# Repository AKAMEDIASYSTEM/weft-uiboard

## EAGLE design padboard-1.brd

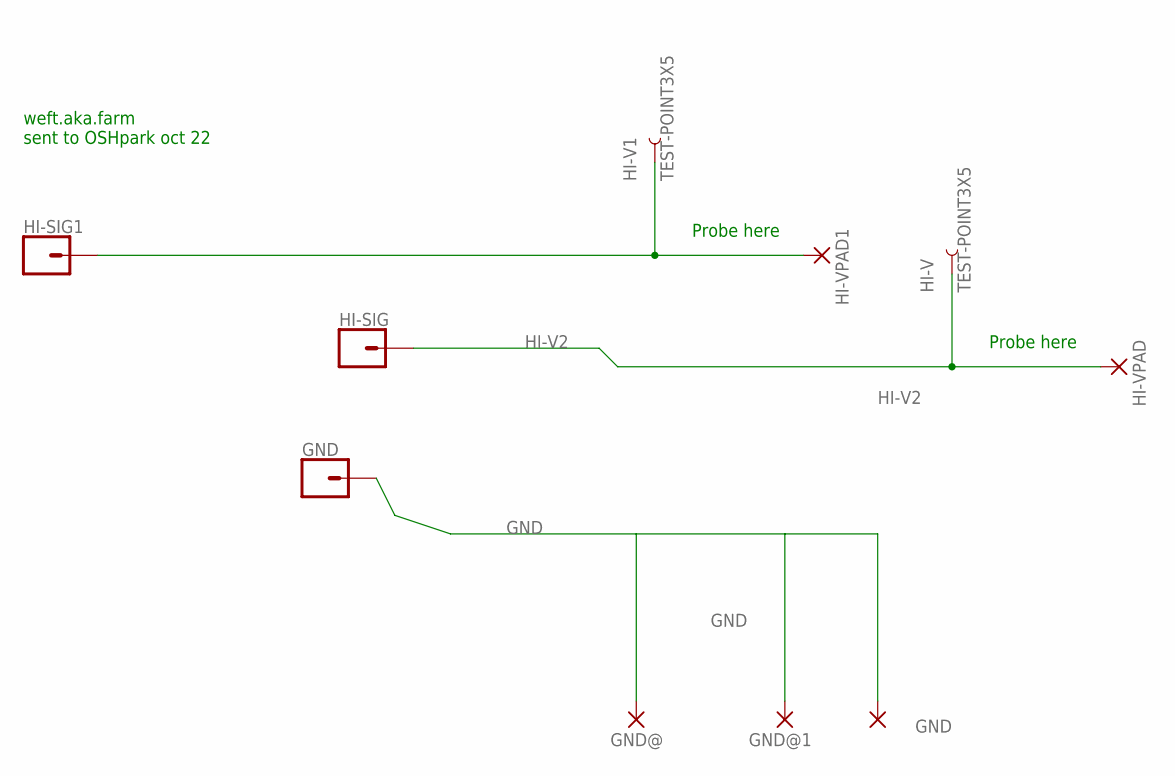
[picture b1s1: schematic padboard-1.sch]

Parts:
GND: CONN_01PTH_LONGPAD; 1X01_LONGPAD
GND@, GND@1, GND@2: WIREPADSMD5-2,5; 5-2,5
HI-SIG, HI-SIG1: CONN_01PTH_LONGPAD; 1X01_LONGPAD
HI-V, HI-V1: TEST-POINT3X5; PAD.03X.05
HI-VPAD, HI-VPAD1: WIREPADSMD5-2,5; 5-2,5

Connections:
GND: GND@.1, GND@1.1, GND@2.1
HI-V1: HI-SIG1.1, HI-V1.P$1, HI-VPAD1.1
HI-V2: HI-SIG.1, HI-V.P$1, HI-VPAD.1

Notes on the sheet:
Probe here
weft.aka.farm sent to OSHpark oct 22

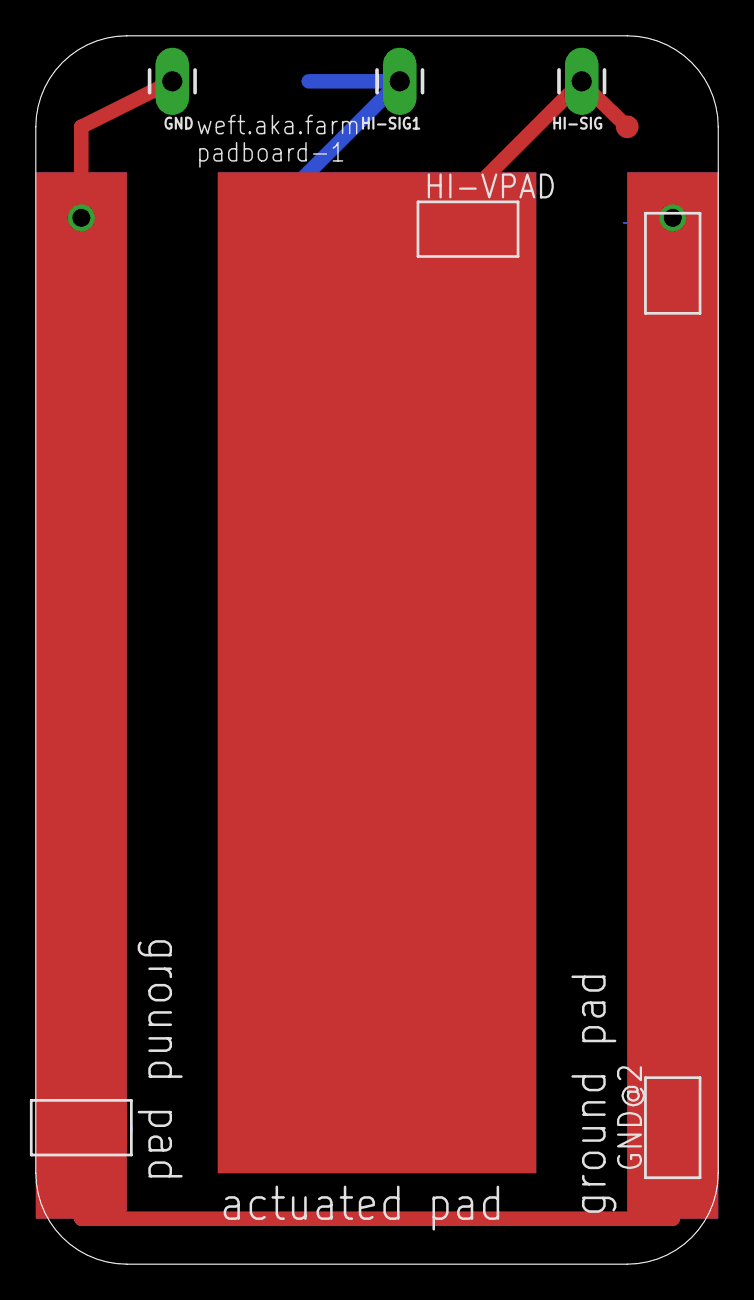
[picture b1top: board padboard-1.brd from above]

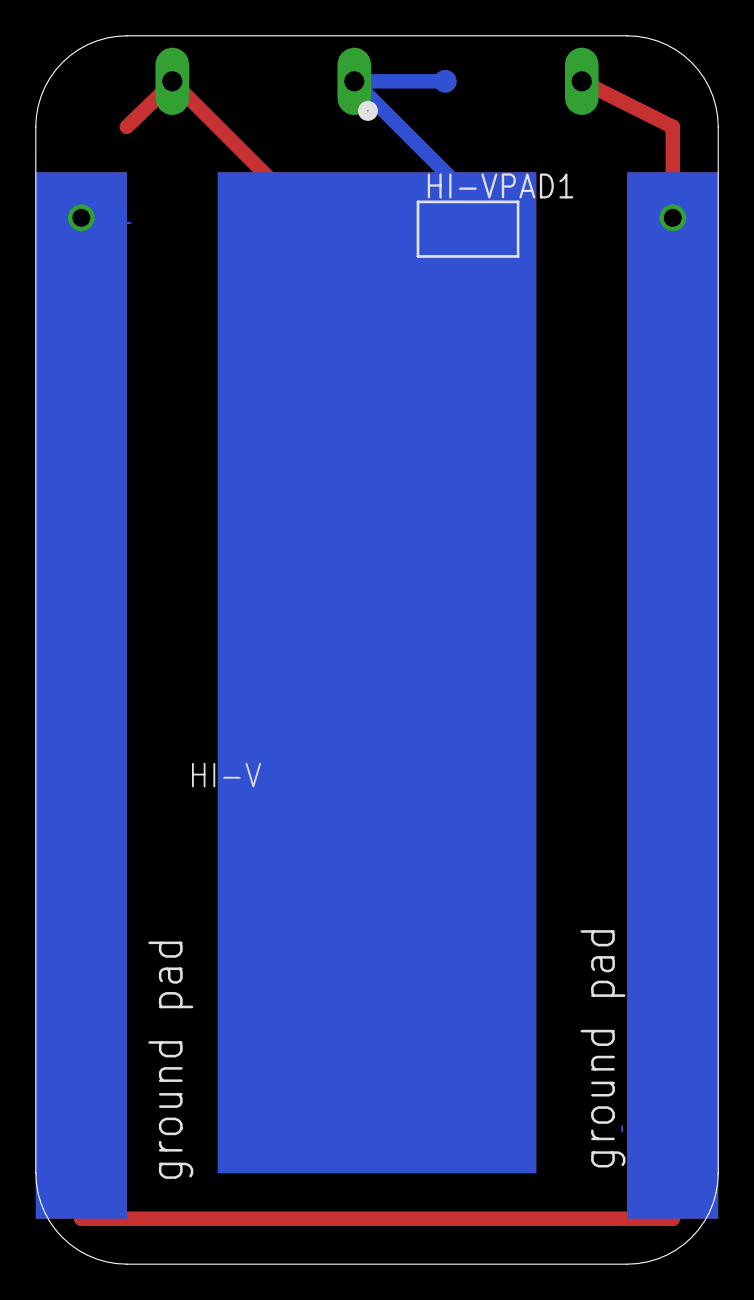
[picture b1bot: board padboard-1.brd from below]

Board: 2 copper layers, 38.1 x 68.6 mm, 10 parts (2 on the bottom side), 3 nets.

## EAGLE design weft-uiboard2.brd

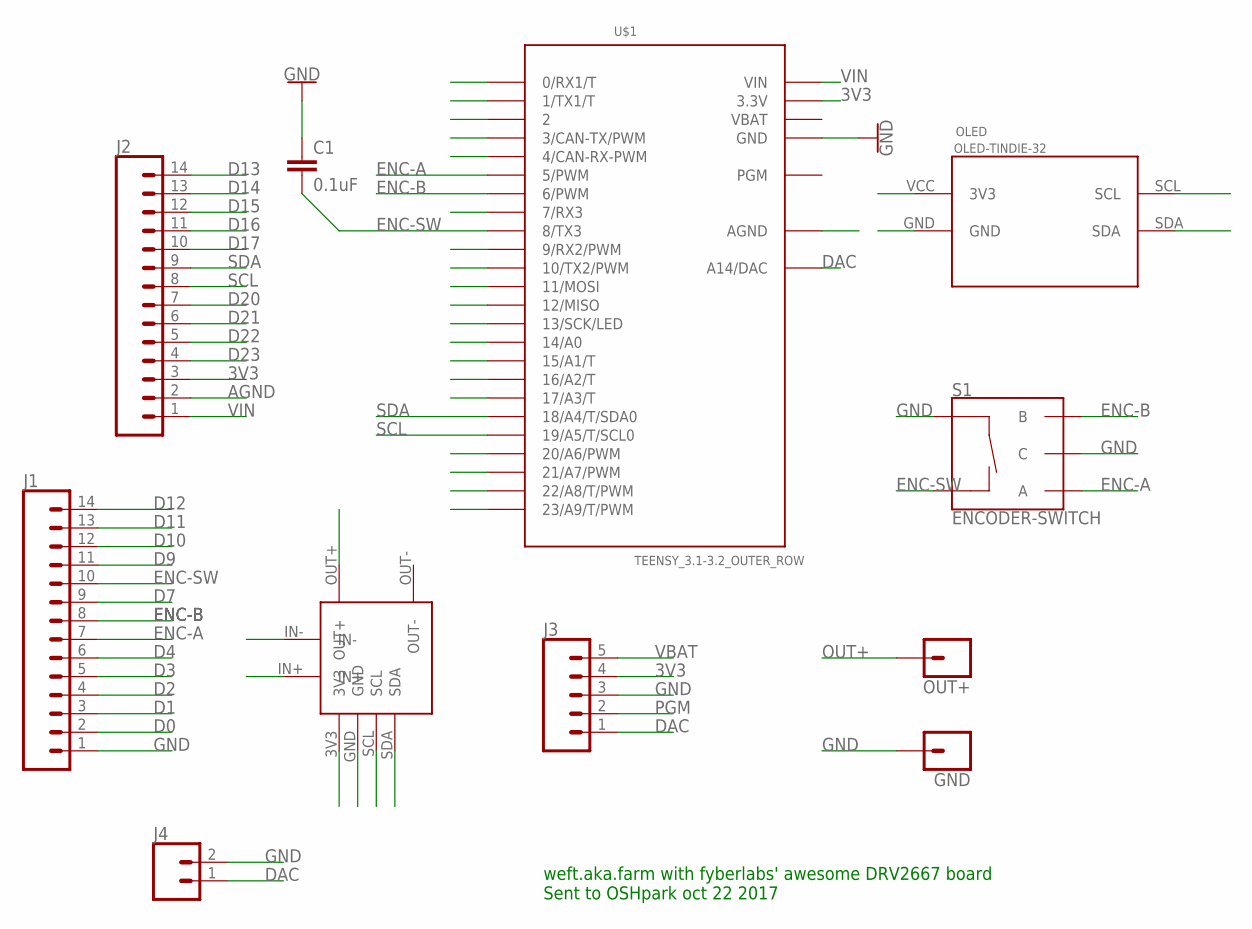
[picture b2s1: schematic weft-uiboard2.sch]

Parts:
C1: 0.1uF; 0805
DRV2667: fyberlabs!; DRV2667-TINDIE
GND: CONN_01OFFSET; 1X01_OFFSET
J1, J2: CONN_14LOCK_LONGPADS; 1X14_LOCK_LONGPADS
J3: CONN_05LOCK_LONGPADS; 1X05_LOCK_LONGPADS
J4: CONN_02LOCK_LONGPADS; 1X02_LOCK_LONGPADS
OLED: OLED-TINDIE-32
OUT+: CONN_01OFFSET; 1X01_OFFSET
S1: ENCODER-SWITCH; ROTARY_ENC_PLAIN
U$1: TEENSY_3.1-3.2_OUTER_ROW; TEENSY_3.0-3.2&LC_OUTER_ROW

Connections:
3V3: DRV2667.3V3, J2.3, J3.4, OLED.VCC (3V3), U$1.3.3V, U$1.3.3V1 (3.3V)
AGND: J2.2, U$1.AGND
D0: J1.2, U$1.0 (0/RX1/T)
D1: J1.3, U$1.1 (1/TX1/T)
D2: J1.4, U$1.2
D3: J1.5, U$1.3 (3/CAN-TX/PWM)
D4: J1.6, U$1.4 (4/CAN-RX-PWM)
D7: J1.9, U$1.7 (7/RX3)
D9: J1.11, U$1.9 (9/RX2/PWM)
D10: J1.12, U$1.10 (10/TX2/PWM)
D11: J1.13, U$1.11 (11/MOSI)
D12: J1.14, U$1.12 (12/MISO)
D13: J2.14, U$1.13 (13/SCK/LED)
D14: J2.13, U$1.14/A0
D15: J2.12, U$1.15/A1 (15/A1/T)
D16: J2.11, U$1.16/A2 (16/A2/T)
D17: J2.10, U$1.17/A3 (17/A3/T)
D20: J2.7, U$1.20/A6 (20/A6/PWM)
D21: J2.6, U$1.21/A7 (21/A7/PWM)
D22: J2.5, U$1.22/A8 (22/A8/T/PWM)
D23: J2.4, U$1.23/A9 (23/A9/T/PWM)
DAC: DRV2667.IN+, J3.1, J4.1, U$1.RESET/DAC (A14/DAC)
ENC-A: J1.7, S1.A, U$1.5 (5/PWM)
ENC-B: J1.8, S1.B, U$1.6 (6/PWM)
ENC-SW: C1.2, J1.10, S1.SW-, U$1.8 (8/TX3)
GND: C1.1, DRV2667.GND, DRV2667.IN-, GND.1, J1.1, J3.3, J4.2, OLED.GND, S1.C, S1.SW+, U$1.GND, U$1.GND1 (GND)
OUT+: DRV2667.OUT+, OUT+.1
PGM: J3.2
SCL: DRV2667.SCL, J2.8, OLED.SCL, U$1.19/A5 (19/A5/T/SCL0)
SDA: DRV2667.SDA, J2.9, OLED.SDA, U$1.18/A4 (18/A4/T/SDA0)
VBAT: J3.5, U$1.VBAT
VIN: J2.1, U$1.VIN

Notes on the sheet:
weft.aka.farm with fyberlabs' awesome DRV2667 board Sent to OSHpark oct 22 2017

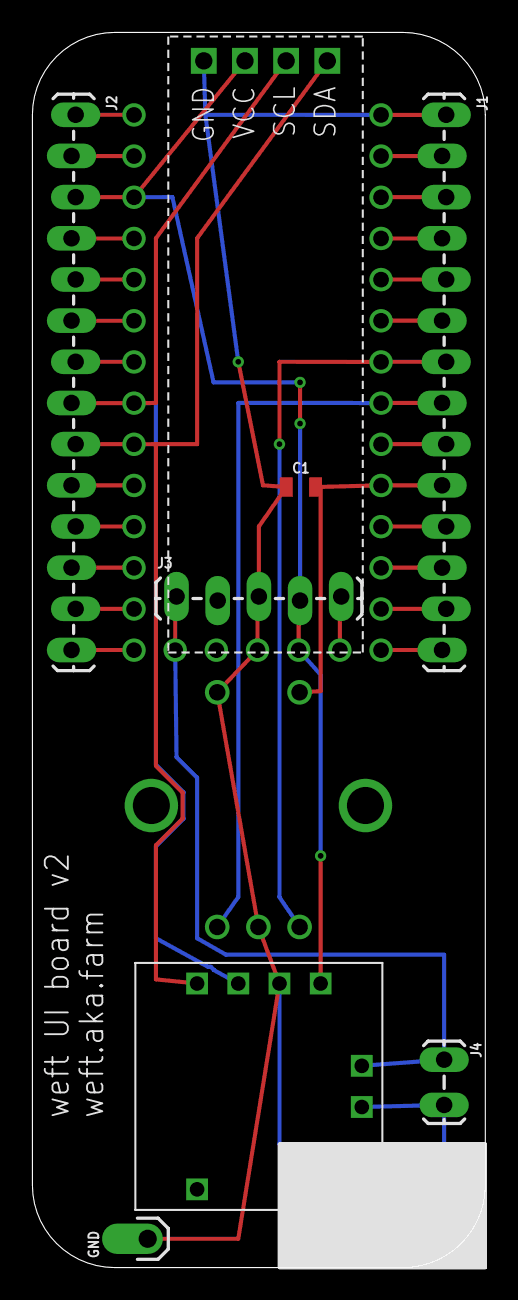
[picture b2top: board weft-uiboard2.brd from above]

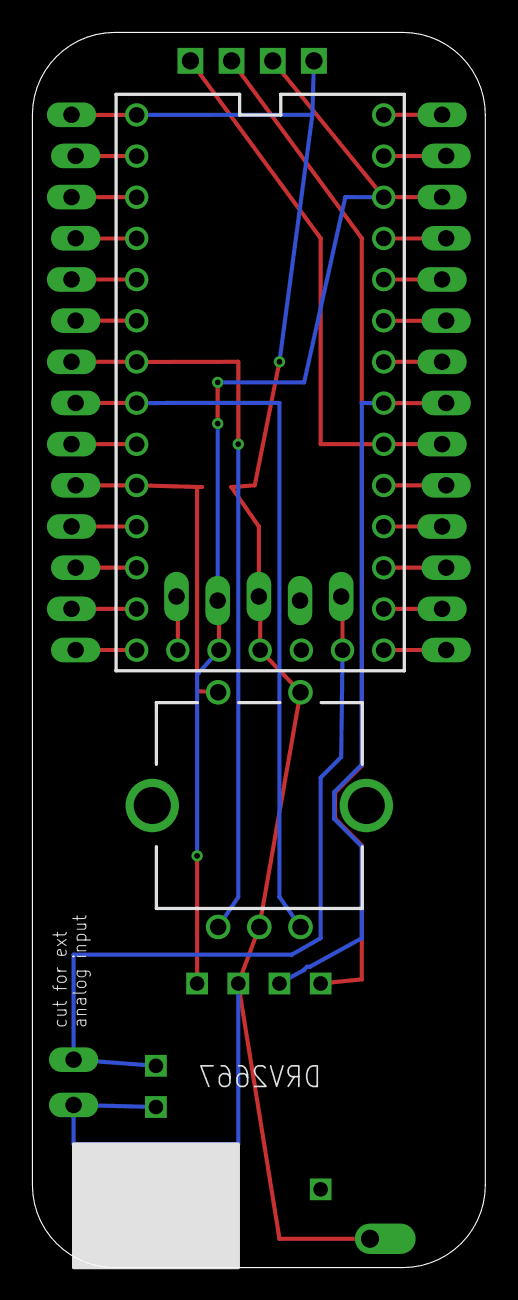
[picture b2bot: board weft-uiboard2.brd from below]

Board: 2 copper layers, 27.9 x 76.2 mm, 11 parts (2 on the bottom side), 31 nets.

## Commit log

2017-09-23 stubbing out OLED and encoder subsystem
2017-11-05 updating with latest uiboard firmware
2017-11-06 general update
2017-11-09 making this the repo for the WEFT UI Board files. The firmware was moved to the /Examples folder of weftlib repo
2017-11-09 adding electrode boardfiles as well

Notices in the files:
parts and their libraries:
SparkFun-Passives: Licensing: Creative Commons ShareAlike 4.0 International - https://creativecommons.org/licenses/by-sa/4.0
